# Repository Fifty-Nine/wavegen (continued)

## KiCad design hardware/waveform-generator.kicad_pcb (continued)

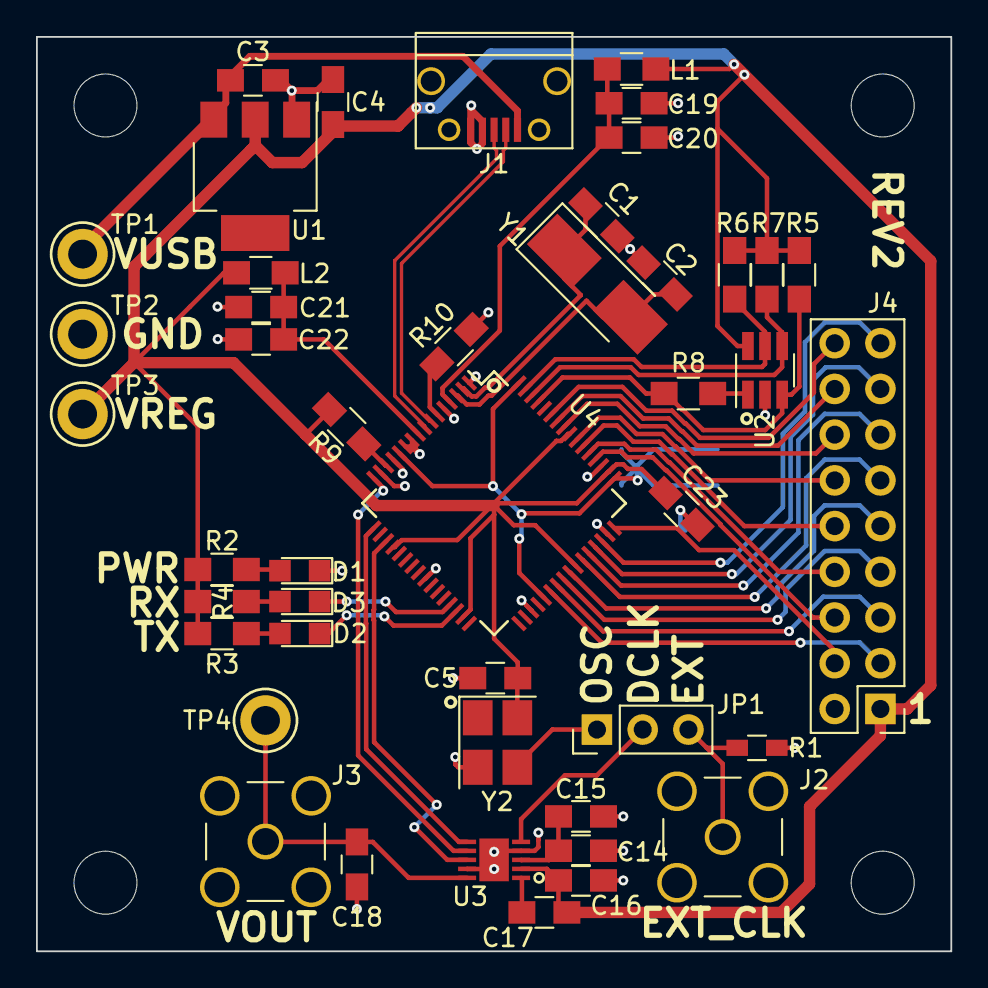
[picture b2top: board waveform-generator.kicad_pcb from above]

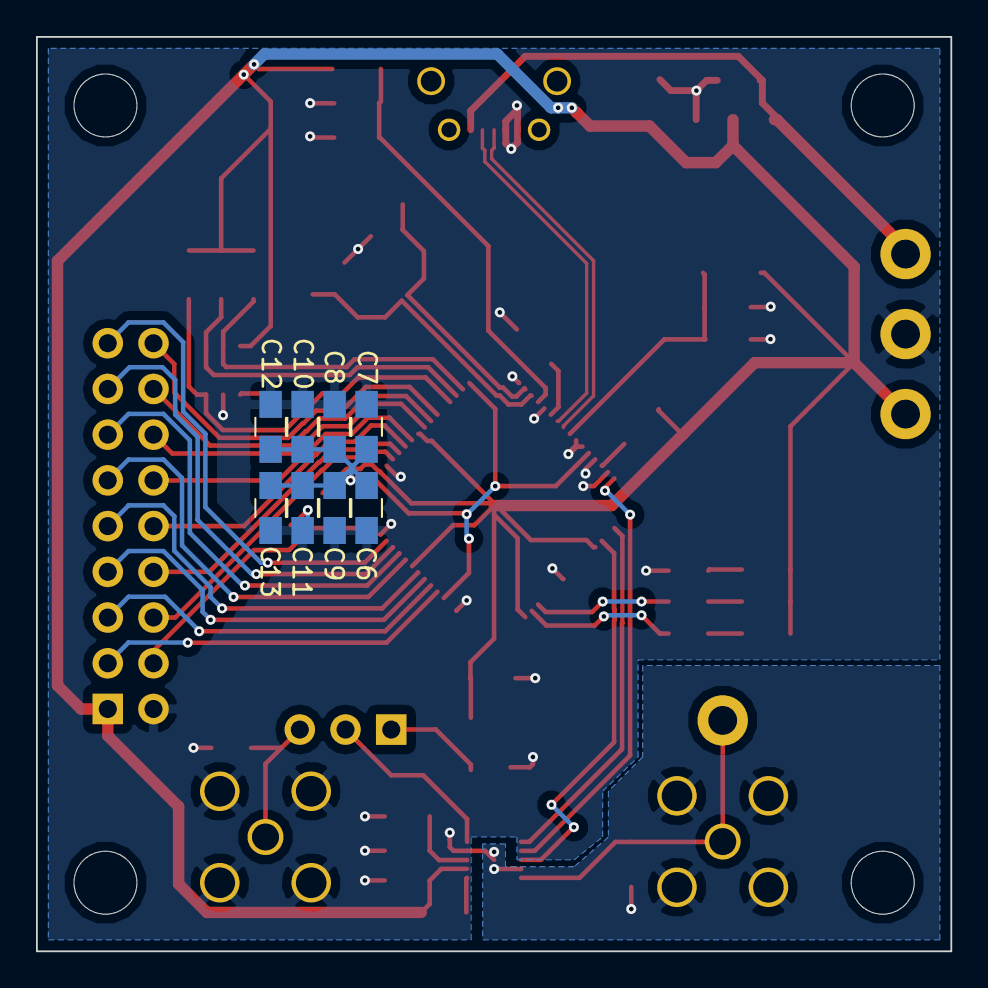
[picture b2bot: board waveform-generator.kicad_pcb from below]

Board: 2 copper layers, 50.8 x 50.8 mm, 53 parts (8 on the bottom side), 46 nets.

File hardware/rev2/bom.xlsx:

Id | Designator | Designation | Quantity | Digikey Part Number
1 | J1 | USB_B | 1 | 609-4618-1-ND
2 | C1, C2 | 27p | 2 | 478-10518-1-ND
3 | C3,C5,C7-C14,C16,C18,C20,C22,C23 | 100n | 15 | 478-1395-1-ND
4 | C4,C15 | 10u | 2 | 478-10568-1-ND
5 | C6 | 3.3u | 1 | 478-1414-1-ND
6 | C17 | 10n | 1 | 478-10447-1-ND
7 | C19,C21 | 4.7u | 2 | 478-1415-1-ND
8 | D1-D3 | LED_Small | 3 | 350-2900-ND,
9 | J2 | EXT_CLK | 1 | A97594-ND
10 | J3 | VOUT | 1 | A97594-ND
11 | J4 | CONN_02X09 | 1 | S2011EC-40-ND
12 | JP1 | CLK_SELECT | 1 | Junk drawer
13 | L1,L2 | 800m | 2 | 490-1054-1-ND
14 | R1 | 50 | 1 | FC0603-50BFCT-ND
15 | R2,R3,R4 | 470 | 3 | P470ADCT-ND
16 | R5,R6,R7 | 10k | 3 | P10KADCT-ND
17 | R8 | 2.2k | 1 | P2.2KADCT-ND
18 | R9 | 1k | 1 | P1.0KADCT-ND
19 | R10 | 12k | 1 | P12KADCT-ND
20 | U1 | LD1117S33TR | 1 | 497-1242-1-ND
21 | U2 | 93LC46BT | 1 | 93LC46BT-I/OTCT-ND
22 | U3 | AD9837 | 1 | AD9837BCPZ-RL7CT-ND
23 | U4 | FT2232H | 1 | 768-1024-1-ND
24 | Y1 | 12MHz | 1 | 535-10634-1-ND
25 | Y2 | OXETGCJANF | 1 | 1664-1111-1-ND
26 | TP1 | VBUS | 1 | 36-5009-ND
27 | TP2 | GND | 1 | 36-5006-ND
28 | TP3 | +3.3V | 1 | 36-5005-ND
29 | TP4 | VOUT | 1 | 36-5121-ND

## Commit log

2017-04-07 Initial commit.
2017-04-08 Replace slots with holes.
2017-04-08 Add gerbers.
2017-04-10 Fixup analog-digital ground connection.
2017-04-17 Add prototype control software.
2017-04-18 Add FTDI eeprom template.
2017-04-18 Add orientation marks to silkscreen.
2017-04-19 Make build more portable.
2017-04-19 Fixes for GCC 4.9 compatibility.
2017-04-19 Add hardware-specific license.
2017-04-19 Add some poor documentation.
2017-04-19 Fixup build command formatting.
2017-04-19 Lose the README header.
2017-04-19 Set theme jekyll-theme-leap-day
2017-04-19 Add design files for the rev1 hardware.
2017-04-19 Actually, maybe I like the header.
2017-04-19 Remove source from gh-pages branch.
2017-04-19 Use absolute links in the readme.
2017-04-19 Remove gh-pages-specific stuff from master.
2017-04-19 Add some notes for a future rev3.
2017-04-19 Move AD9837-specific stuff into its own file.
2017-04-19 Add a method to set the master clock frequency.
2017-04-21 Move wavegen_error into separate header.
2017-04-21 Move packet into its own file.
2017-04-21 Add CMake logic to fall back to FTD2XX.
2017-04-21 Refactor FTDI-specific logic to allow swapping out driver libraries.
2017-04-21 Add stub for D2XX-based SPI.
2017-04-21 Get stuff building with visual studio, implement LibMPSSE-SPI wrapper.
2017-04-22 Add python bindings.
2017-04-22 Initial rev3 work.
2017-04-22 Use portable sleep in wavegen-test
2017-04-22 Fixes for building on windows.
2017-04-22 Fix windows command line cmake build.
2017-04-22 More windows hacking.
2017-04-22 Add install targets.
2017-04-23 Add AD9102 to the schematic.
2017-04-24 Add initial output amplifier design.
2017-04-24 Add bypass caps to output amp.
    Fixes #4.
2017-04-26 Add an additional output stage to the amplifier sim.
2017-04-26 Add ltspice gitignore.
2017-04-26 Fixup the fab layers to make component values visible.
2017-04-26 Implement '__del__' in python bindings.
    Fixes #5
2017-04-27 Get python installation right.
2017-04-28 Add missing footprints.
2017-04-28 Finish up output amp schematic.
2017-04-28 Make some progress on layout.
2017-04-29 Fix incorrect connection to output amp.
2017-04-29 Add 3.2x2.5 oscillator footprint
2017-04-29 Add decoupling to biasing amp.
2017-04-29 Fixup USB footprint shield pin.
2017-04-29 Fixup vreg decoupling.
2017-04-29 Initial placement.
2017-04-29 First routing attempt.
2017-04-29 Replace rev1 image with rev2.
2017-04-29 Update component selection based on digikey availability.
2017-04-29 Continue iterating on layout.
2017-05-02 Initial attempt at a complete layout.
2017-05-02 Final touches.
2017-05-02 Generate gerbers.
2017-05-02 Add a script to make the gerbers Seeedstudio-friendly.
2017-05-07 Move OSHW logo. Add github link.
2017-05-07 Add BOM for rev2.
2017-05-07 Add ability to filter devices by serial.
2017-05-07 Add a way to query the library version.
2017-05-07 Rework how we get the git revision.
2017-05-07 Refactor device::setOutput
2017-05-07 Refactor FTDI stuff into a separate namespace.
2017-05-07 Extend lifetime of ftdi_context instance.
2017-05-07 Allow for multiple connected devices.
2017-05-08 Add a basic gui interface.
2017-05-10 Output the correct frequency for square waves.
    Fixes #1.
